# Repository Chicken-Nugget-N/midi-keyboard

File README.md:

# midi-keyboard
midi keyboard designed on kicad and arduino ide
MIDI Keyboard PCB
Overview

This project contains the PCB design for a MIDI keyboard controller. The board layout is designed to organize the electronic components and connections required for a keyboard-based MIDI interface.

Features
Multiple input buttons or switches
Dedicated component areas for control electronics
Custom PCB layout and copper routing
Organized component footprints and connection pads
Silkscreen labels for component identification

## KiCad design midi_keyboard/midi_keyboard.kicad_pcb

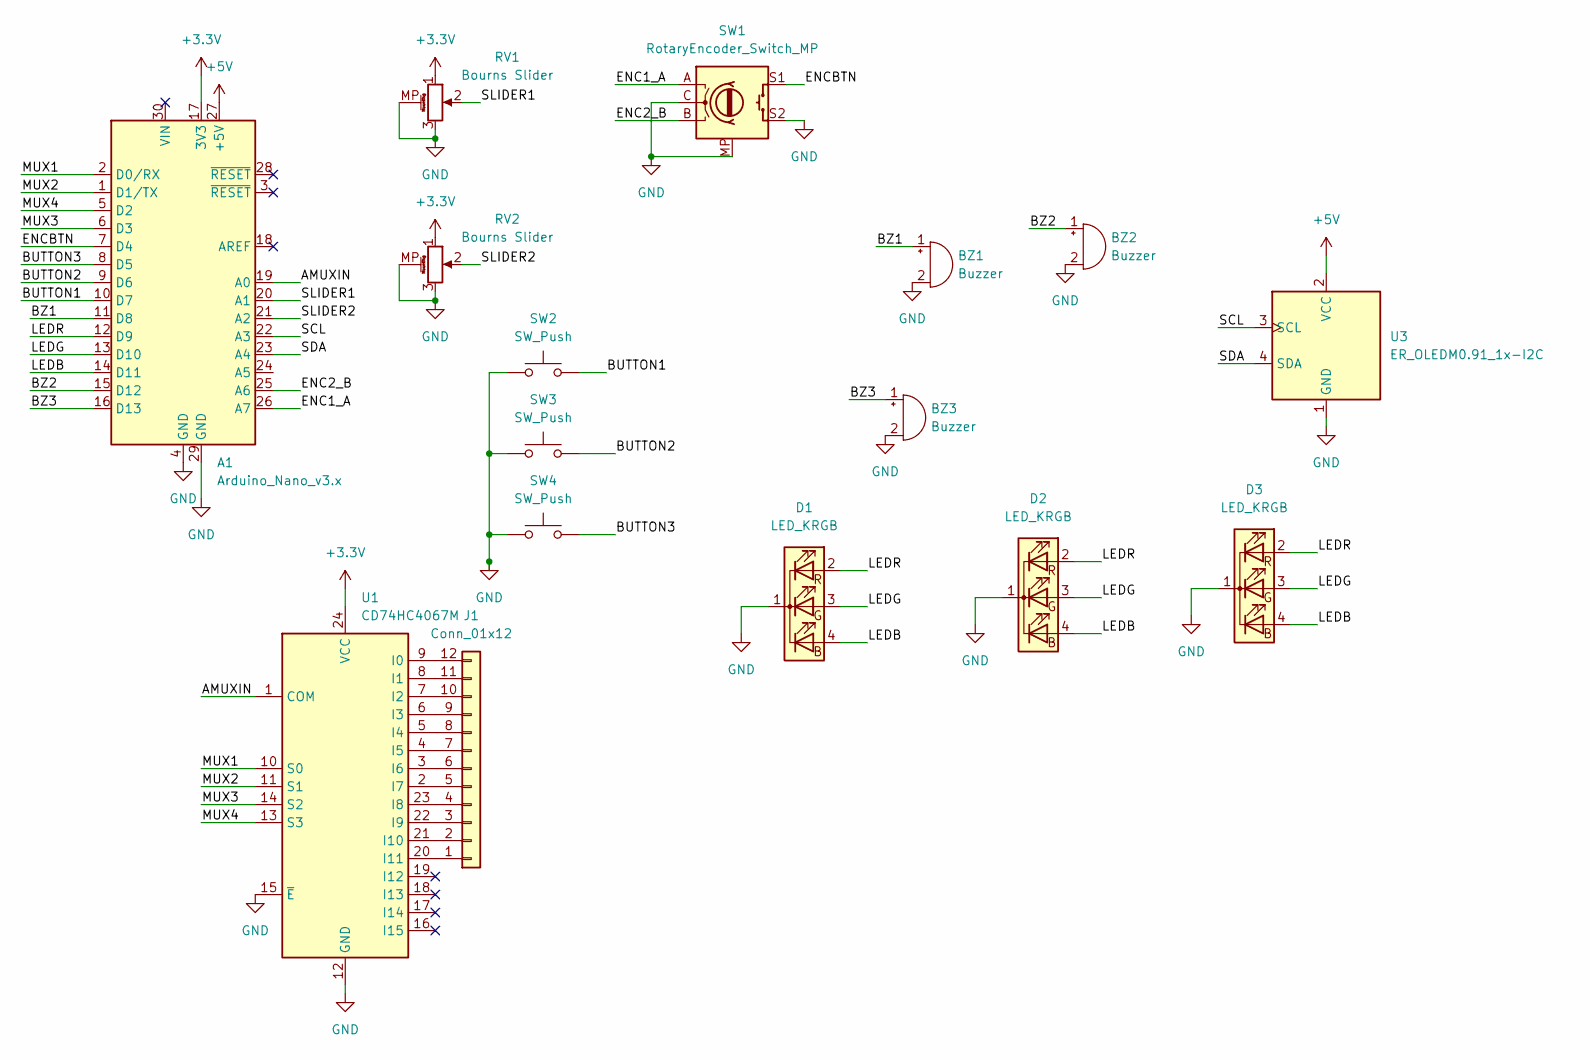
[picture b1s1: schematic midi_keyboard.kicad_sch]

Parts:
A1: Arduino_Nano_v3.x; Arduino_Nano
BZ1, BZ2, BZ3: Buzzer; Buzzer_12x9.5RM7.6
D1, D2, D3: LED_KRGB; PinSocket_1x04_P2.54mm_Vertical
J1: Conn_01x12; capacitive_keys
RV1, RV2: Bourns Slider; Potentiometer_Bourns_PTA3043_Single_Slide
SW1: RotaryEncoder_Switch_MP; RotaryEncoder_Alps_EC11E-Switch_Vertical_H20mm
SW2, SW3, SW4: SW_Push; SW_Cherry_MX_1.00u_PCB
U1: CD74HC4067M; MODULE_BOB-09056
U3: ER_OLEDM0.91_1x-I2C

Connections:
+3.3V: A1.17 (3V3), RV1.1, RV2.1, U1.24 (VCC)
+5V: A1.27 (+5V), U3.2 (VCC)
/AMUXIN: A1.19 (A0), U1.1 (COM)
/BUTTON1: A1.10 (D7), SW2.2
/BUTTON2: A1.9 (D6), SW3.2
/BUTTON3: A1.8 (D5), SW4.2
/BZ1: A1.11 (D8), BZ1.1 (+)
/BZ2: A1.15 (D12), BZ2.1 (+)
/BZ3: A1.16 (D13), BZ3.1 (+)
/ENC1_A: A1.26 (A7), SW1.A
/ENC2_B: A1.25 (A6), SW1.B
/ENCBTN: A1.7 (D4), SW1.S1
/LEDB: A1.14 (D11), D1.4 (BA), D2.4 (BA), D3.4 (BA)
/LEDG: A1.13 (D10), D1.3 (GA), D2.3 (GA), D3.3 (GA)
/LEDR: A1.12 (D9), D1.2 (RA), D2.2 (RA), D3.2 (RA)
/MUX1: A1.2 (D0/RX), U1.10 (S0)
/MUX2: A1.1 (D1/TX), U1.11 (S1)
/MUX3: A1.6 (D3), U1.14 (S2)
/MUX4: A1.5 (D2), U1.13 (S3)
/SCL: A1.22 (A3), U3.3 (SCL)
/SDA: A1.23 (A4), U3.4 (SDA)
/SLIDER1: A1.20 (A1), RV1.2
/SLIDER2: A1.21 (A2), RV2.2
GND: A1.4 (GND), A1.29 (GND), BZ1.2 (-), BZ2.2 (-), BZ3.2 (-), D1.1 (K), D2.1 (K), D3.1 (K), RV1.3, RV1.MP (MountPin), RV2.3, RV2.MP (MountPin), SW1.C, SW1.MP, SW1.S2, SW2.1, SW3.1, SW4.1, U1.12 (GND), U1.15 (~E), U3.1 (GND)
unnamed: J1.1, U1.20 (I11)
unnamed: J1.2, U1.21 (I10)
unnamed: J1.3, U1.22 (I9)
unnamed: J1.4, U1.23 (I8)
unnamed: J1.5, U1.2 (I7)
unnamed: J1.6, U1.3 (I6)
unnamed: J1.7, U1.4 (I5)
unnamed: J1.8, U1.5 (I4)
unnamed: J1.9, U1.6 (I3)
unnamed: J1.10, U1.7 (I2)
unnamed: J1.11, U1.8 (I1)
unnamed: J1.12, U1.9 (I0)

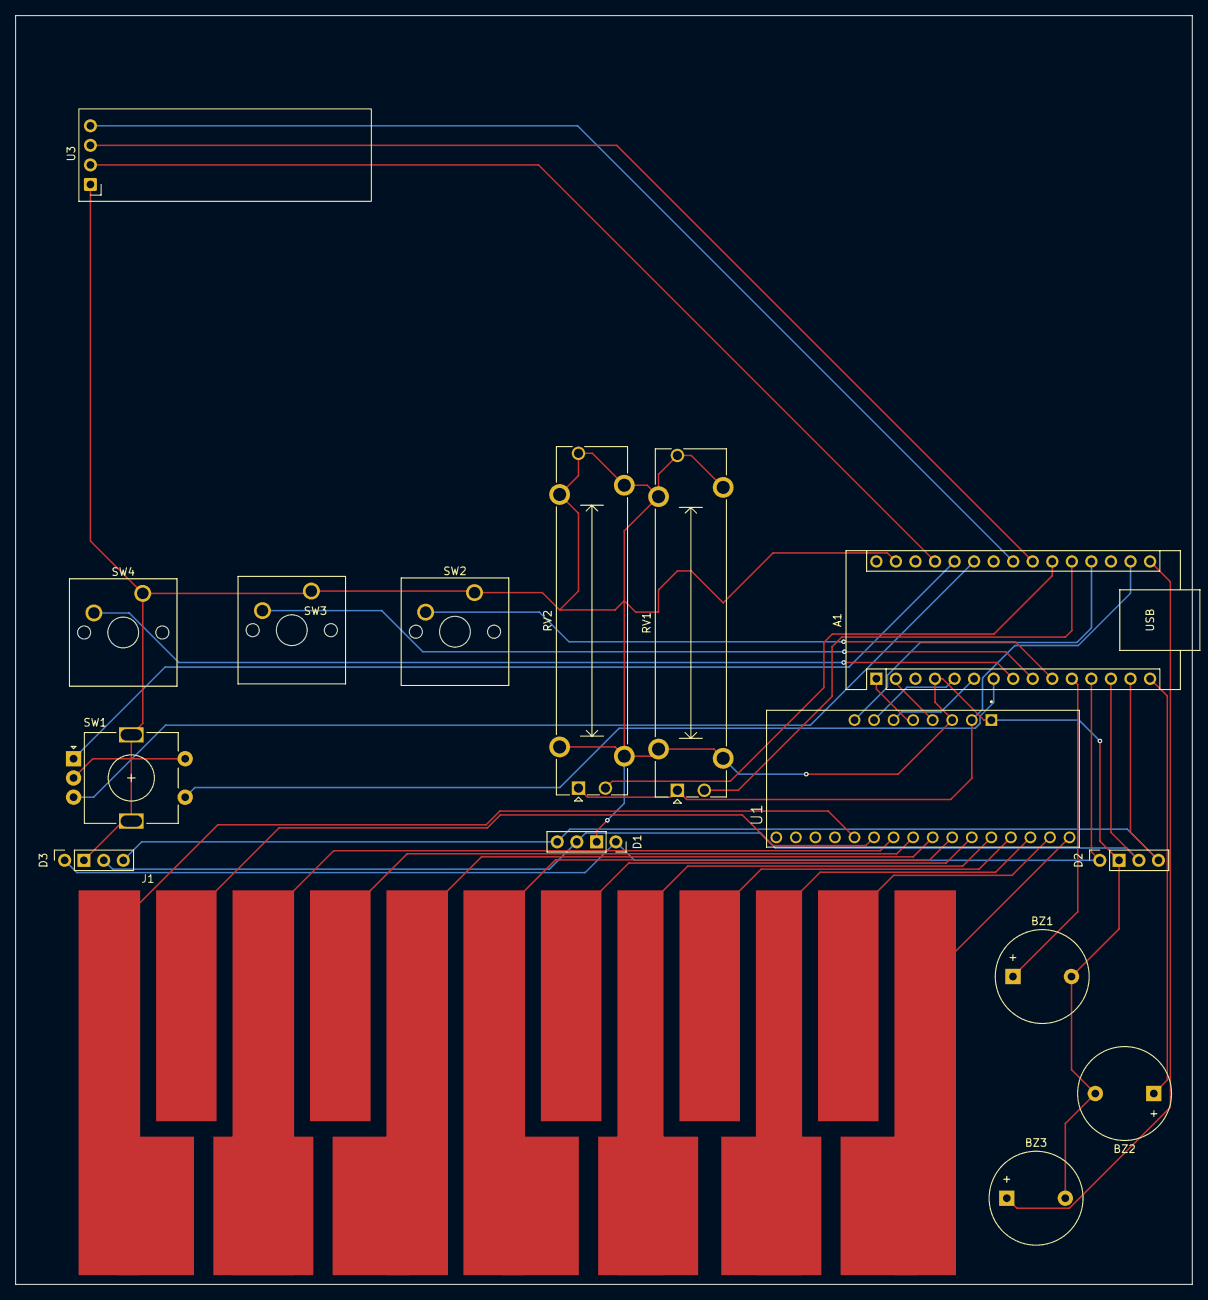
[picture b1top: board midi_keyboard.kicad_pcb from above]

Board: 2 copper layers, 152.9 x 164.9 mm, 16 parts (0 on the bottom side), 36 nets.
